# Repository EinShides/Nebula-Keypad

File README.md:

A small 3 key keypad with a rotary encoder and lcd display. The case is 3d printable and designed to work with m2 threaded inserts (4-5mm). Uses USB C, ESD protection, and GeonWorks tadpole mount. Currently a BOM is in the works.

THIS KEYPAD HAS NOT BEEN TESTED YET.

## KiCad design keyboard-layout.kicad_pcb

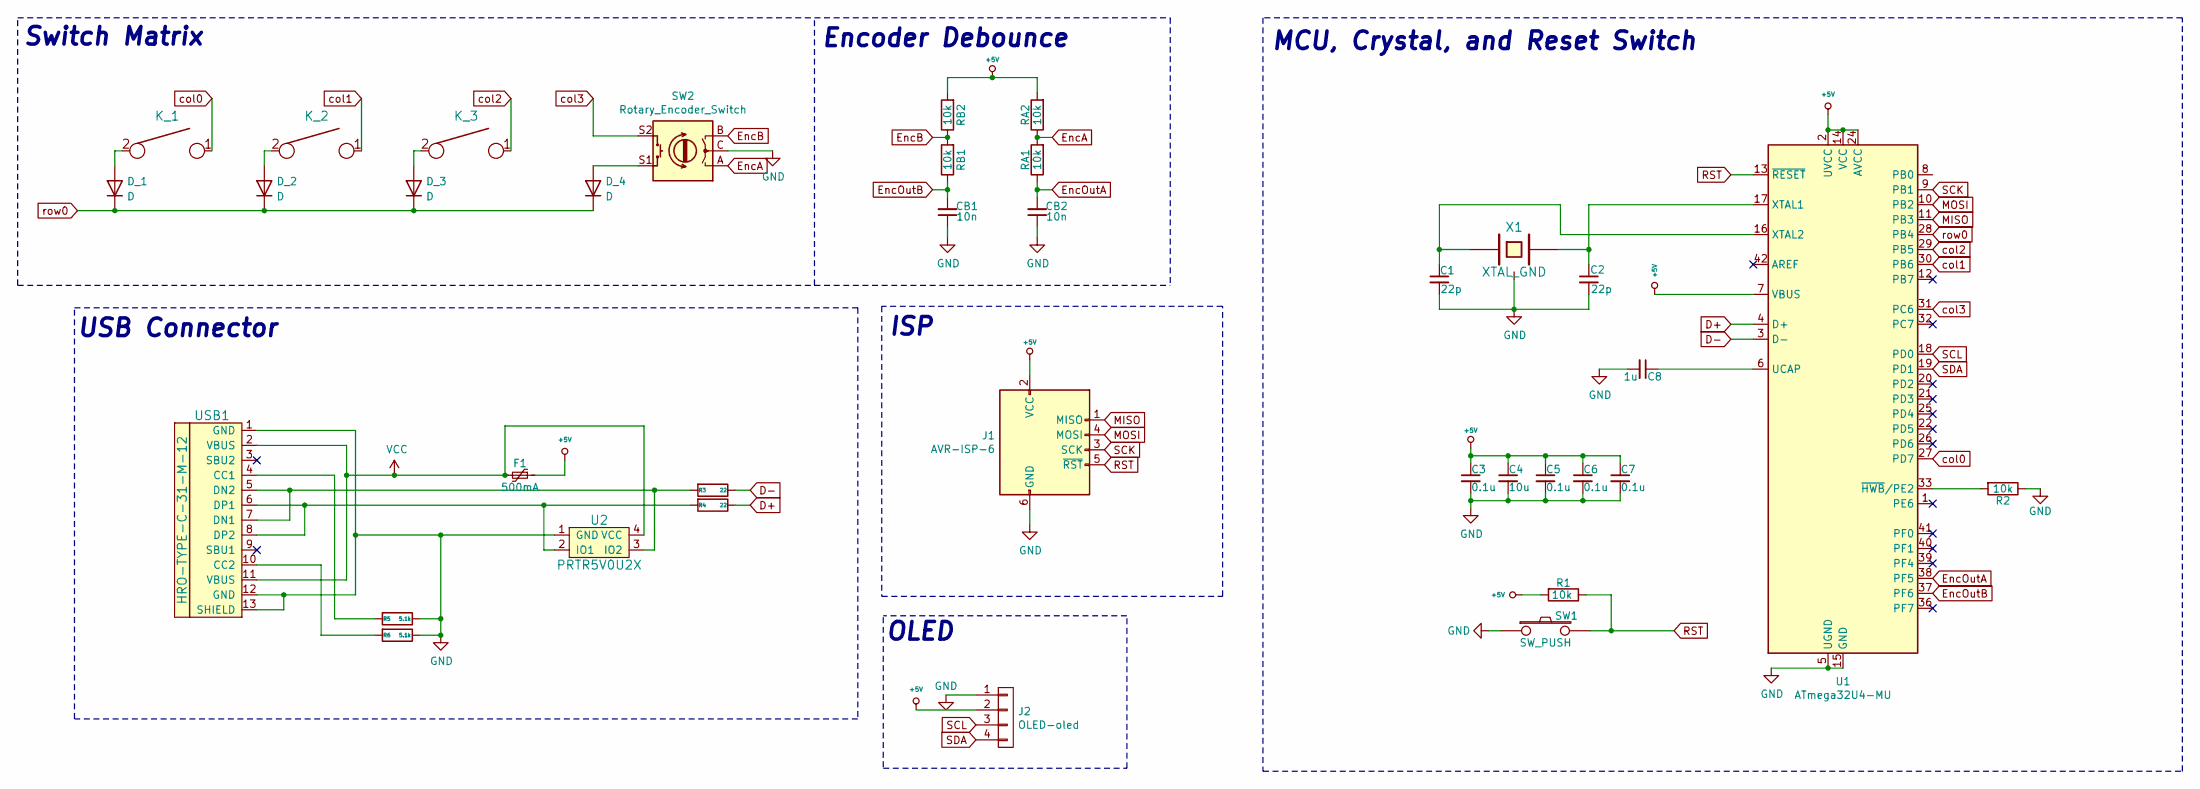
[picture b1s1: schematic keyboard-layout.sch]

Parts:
C1, C2: 22p; C_0603_1608Metric_Pad1.08x0.95mm_HandSolder; LCSC C1653
C3, C5, C6, C7: 0.1u; C_0603_1608Metric_Pad1.08x0.95mm_HandSolder; LCSC C24452
C4: 10u; C_0603_1608Metric_Pad1.08x0.95mm_HandSolder; LCSC C96446
C8: 1u; C_0603_1608Metric_Pad1.08x0.95mm_HandSolder; LCSC C15849
CB1, CB2: 10n; C_0603_1608Metric_Pad1.08x0.95mm_HandSolder; LCSC C15849
D_1, D_2, D_3, D_4: D; D_SOD123_hand; LCSC C64898
F1: 500mA; Fuse_1206_3216Metric_Pad1.42x1.75mm_HandSolder; LCSC C70076
J1: AVR-ISP-6; Reset_Pretty
J2: OLED-oled; OLED_4Pin
K_1, K_2, K_3: KEYSW; MXOnly-1U-NoLED
R1, R2: 10k; R_0805_2012Metric_Pad1.20x1.40mm_HandSolder; LCSC C17414
R3, R4: 22; R_0805_2012Metric_Pad1.20x1.40mm_HandSolder; LCSC C17561
R5, R6: 5.1k; R_0805_2012Metric_Pad1.20x1.40mm_HandSolder; LCSC C27834
RA1, RA2: 10k; R_0805_2012Metric_Pad1.20x1.40mm_HandSolder; LCSC C17414
RB1, RB2: 10k; R_0805_2012Metric_Pad1.20x1.40mm_HandSolder; LCSC C17414
SW1: SW_PUSH; Jumper-UserFriendly
SW2: Rotary_Encoder_Switch; ALPS_EC11E
U1: ATmega32U4-MU; QFN-44-1EP_7x7mm_P0.5mm_EP5.2x5.2mm; LCSC C45874
U2: PRTR5V0U2X; SOT143B; LCSC C316030
USB1: HRO-TYPE-C-31-M-12; HRO-TYPE-C-31-M-12-HandSoldering; LCSC C165948
X1: XTAL_GND; crystal_FA238-TSX3225; LCSC C89371

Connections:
+5V: C3.1, C4.1, C5.1, C6.1, C7.1, F1.1, J1.2 (VCC), J2.2, R1.2, RA2.2, RB2.2, U1.2 (UVCC), U1.7 (VBUS), U1.14 (VCC), U1.24 (AVCC), U1.34 (VCC), U1.44 (AVCC)
D+: R4.1, U1.4 (D+)
D-: R3.1, U1.3 (D-)
EncA: RA1.2, RA2.1, SW2.A
EncB: RB1.2, RB2.1, SW2.B
EncOutA: CB2.2, RA1.1, U1.38 (PF5)
EncOutB: CB1.2, RB1.1, U1.37 (PF6)
GND: C1.2, C2.2, C3.2, C4.2, C5.2, C6.2, C7.2, C8.2, CB1.1, CB2.1, J1.6 (GND), J2.1, R2.1, R5.1, R6.1, SW1.1, SW2.C, U1.5 (UGND), U1.15 (GND), U1.23 (GND), U1.35 (GND), U1.43 (GND), U1.45 (GND), U2.1 (GND), USB1.1 (GND), USB1.12 (GND), USB1.13 (SHIELD), X1.3
MISO: J1.1 (MISO), U1.11 (PB3)
MOSI: J1.4 (MOSI), U1.10 (PB2)
unnamed: C1.1, U1.16 (XTAL2), X1.1
unnamed: C2.1, U1.17 (XTAL1), X1.2
unnamed: C8.1, U1.6 (UCAP)
unnamed: D_1.2 (A), K_1.2
unnamed: D_2.2 (A), K_2.2
unnamed: D_3.2 (A), K_3.2
unnamed: D_4.2 (A), SW2.S1
unnamed: R2.2, U1.33 (~HWB~/PE2)
unnamed: R3.2, U2.3 (IO2), USB1.5 (DN2), USB1.7 (DN1)
unnamed: R4.2, U2.2 (IO1), USB1.6 (DP1), USB1.8 (DP2)
unnamed: R5.2, USB1.4 (CC1)
unnamed: R6.2, USB1.10 (CC2)
RST: J1.5 (~RST), R1.1, SW1.2, U1.13 (~RESET)
SCK: J1.3 (SCK), U1.9 (PB1)
SCL: J2.3, U1.18 (PD0)
SDA: J2.4, U1.19 (PD1)
VCC: F1.2, U2.4 (VCC), USB1.2 (VBUS), USB1.11 (VBUS)
col0: K_1.1, U1.27 (PD7)
col1: K_2.1, U1.30 (PB6)
col2: K_3.1, U1.29 (PB5)
col3: SW2.S2, U1.31 (PC6)
row0: D_1.1 (K), D_2.1 (K), D_3.1 (K), D_4.1 (K), U1.28 (PB4)

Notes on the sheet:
USB Connector
Encoder Debounce
Switch Matrix
ISP
MCU, Crystal, and Reset Switch
OLED

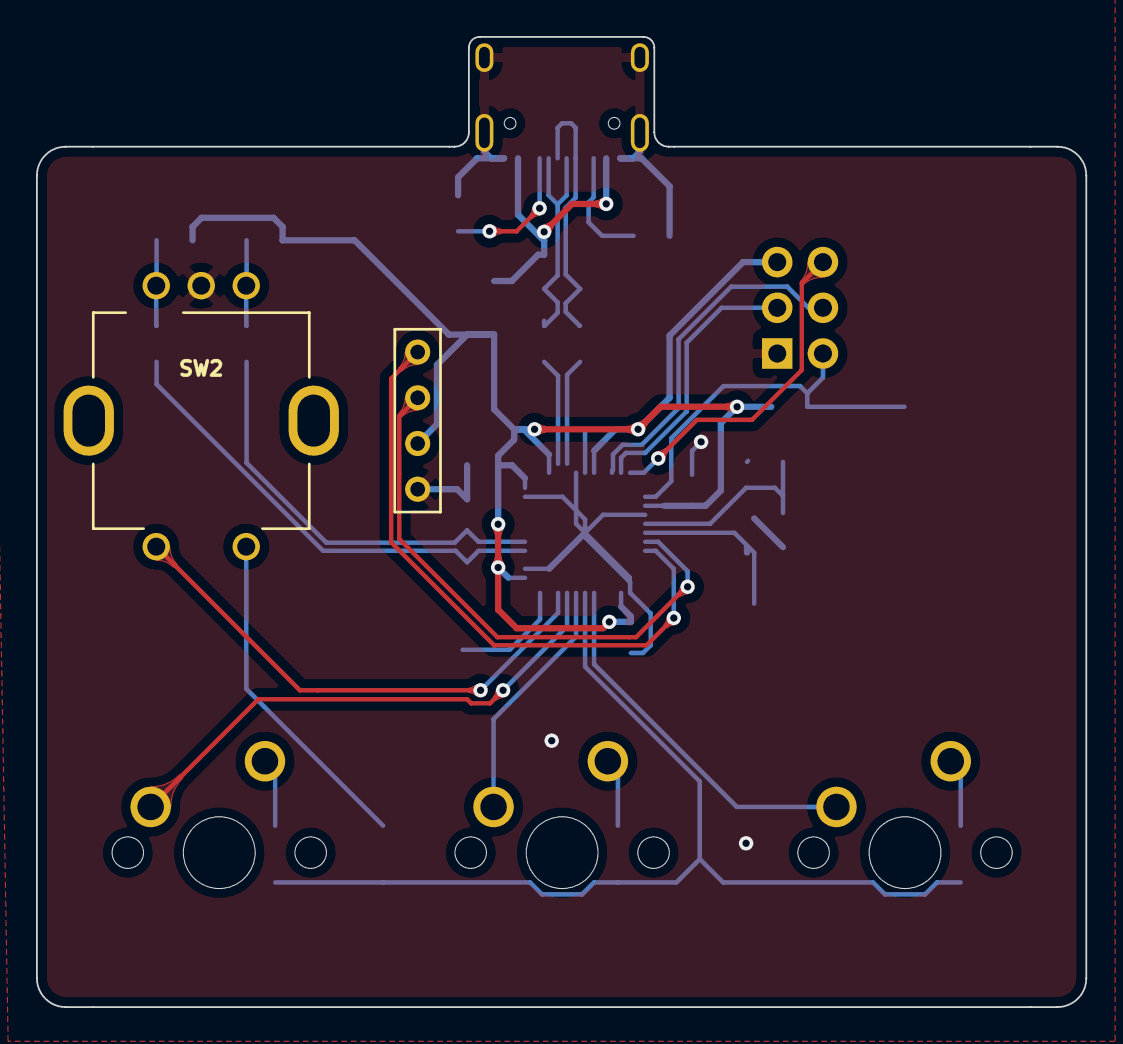
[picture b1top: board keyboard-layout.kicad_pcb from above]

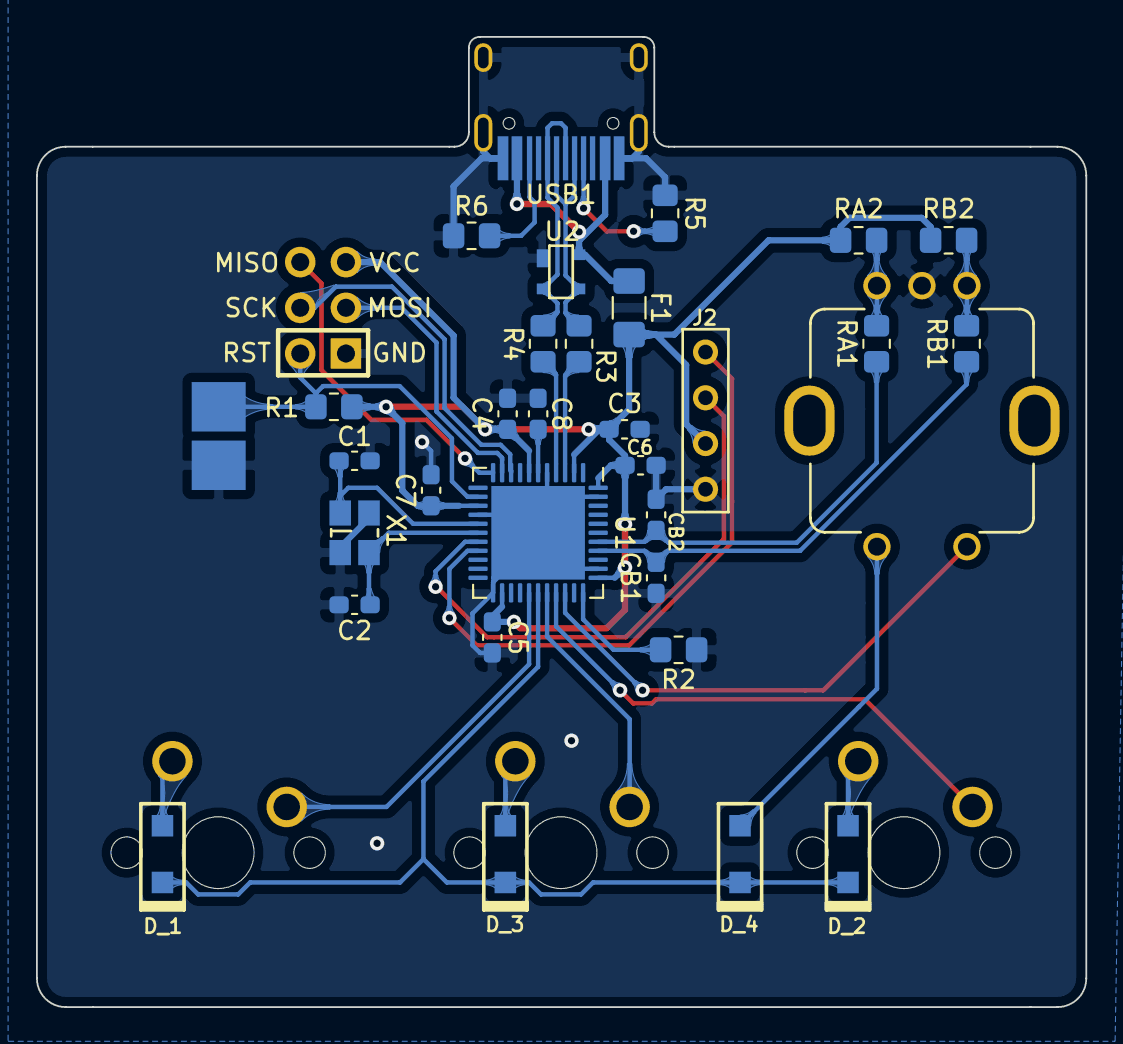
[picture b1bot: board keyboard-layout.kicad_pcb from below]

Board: 2 copper layers, 58.3 x 53.9 mm, 36 parts (32 on the bottom side), 32 nets.
